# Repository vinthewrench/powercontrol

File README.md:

This repository contains a hardware power controller that enforces safe, predictable power-on and power-off behavior for a Raspberry Pi used in real-world automation systems.

It grew out of the work described in [Raspberry Pi Internet of Things – Part 029](https://www.vinthewrench.com/p/raspberry-pi-internet-of-things-part-029), where the problem wasn’t software, but power: a Pi running irrigation, valves, radios, or sensors cannot simply lose power without consequences. Filesystems corrupt, tasks stop mid-cycle, and batteries get drained dry.

The design documented here takes those ideas further by moving power control out of the Pi and into a small, dedicated controller. The Pi decides when it is safe to shut down; the hardware enforces when power is actually applied or removed. A latching relay does the physical switching, while simple signals coordinate startup, shutdown, and recovery when utility power fails or returns.

The result is a Raspberry Pi that behaves like part of a system, not a hobby board dangling from a power supply.
 
## Repository Layout

```
.
├── Power_Controller_Design_Document_v1.1.md
├── README.md
├── code/
│   └── powercontrol/
│       ├── powercontrol.c
│       ├── makefile
│       └── Doxyfile
└── hw/
    └── powercontrol_2.1/
        ├── powercontrol_2.1.kicad_sch
        ├── powercontrol_2.1.kicad_pcb
        ├── powercontrol_2.1.kicad_pro
        ├── powercontrol_2.1.kicad_prl
        └── build.zip
```

---

## Documentation

### Power_Controller_Design_Document_v1.1.md

This is the **authoritative design specification** for this project.

It defines:
- Hardware intent
- Firmware behavior
- I2C command contract
- Extended readback interface (`0xF0`)
- Design philosophy and explicit non-goals

## Firmware (`code/powercontrol`)

### Overview

The firmware runs on an AVR (ATmega8 / ATmega88 class) and provides:

- Latching relay control (pulse-only, never held)
- Manual wake via INT0
- AC_OK wake via INT1
- Red / Green status LEDs
- I2C slave interface (address `0x08`)
- Watchdog-style host supervision
- Low-power IDLE sleep when inactive

The firmware is **single-loop, flag-driven**, and avoids performing real work in ISRs.

### Files

- `powercontrol.c`  
  Main firmware implementation. This is the source of truth.

- `makefile`  
  Minimal AVR-GCC build file. No build system gymnastics.

- `Doxyfile`  
  Optional Doxygen configuration for generating internal documentation.

### Build

Typical workflow:

```
cd code/powercontrol
make
make flash
```

Target MCU, programmer, and fuses are defined in the makefile and are expected to be adjusted per environment.

## Hardware (`hw/powercontrol_2.1`)

This directory contains the **KiCad revision 2.1** of the Power Controller board.

### Hardware Summary

- +12 V input
- On-board 5 V regulator
- AVR MCU running internal 8 MHz RC oscillator
- ULN2003A relay driver
- Dual-coil latching relay
- Manual wake button
- AC_OK external wake input
- I2C interface with series protection resistors
- Explicit power and ground wiring (no hidden pins)

The MCU remains powered at all times so it can observe wake events even when the downstream system is off.

### Fabrication

`build.zip` contains fabrication outputs (Gerbers, drill files, etc.) suitable for board manufacturing.

## I2C Interface (Summary)

- **Address**: `0x08`
- **Write-only commands** for relay and LED control
- **Extended readback** via command `0xF0`

Example:

```
i2ctransfer -y 1 w1@0x08 0xF0 r4
```

Expected response:

```
0x13 status_byte timer_MSB timer_LSB
```

###  I2C Command Set

| Command | Function |
|-------|----------|
| 0x00 | NO-OP watchdog ping |
| 0x01 | Relay OFF |
| 0x02 | Relay ON |
| 0x03 | Red LED OFF |
| 0x04 | Red LED ON |
| 0x05 | Green LED OFF |
| 0x06 | Green LED ON |
| 0x10 | Set ping timeout (uint16 ms) |

---

## Non-Goals

This project explicitly does **not** attempt to provide:

- RTC or scheduling
- Network connectivity
- Filesystems
- Soft power control
- UPS functionality

Those responsibilities belong on the host system.

## Design Intent (Plain English)

If the host behaves, it stays powered.  
If it locks up, it gets cut off and restarted.  
If a human presses the button, power comes on.  
If AC disappears, the system reacts predictably.

## License

- **Firmware / Software**: MIT License  
- **Hardware designs**: CERN-OHL-P v2 (Permissive Open Hardware Licence)

Copyright © 2026 Vinnie Moscaritolo

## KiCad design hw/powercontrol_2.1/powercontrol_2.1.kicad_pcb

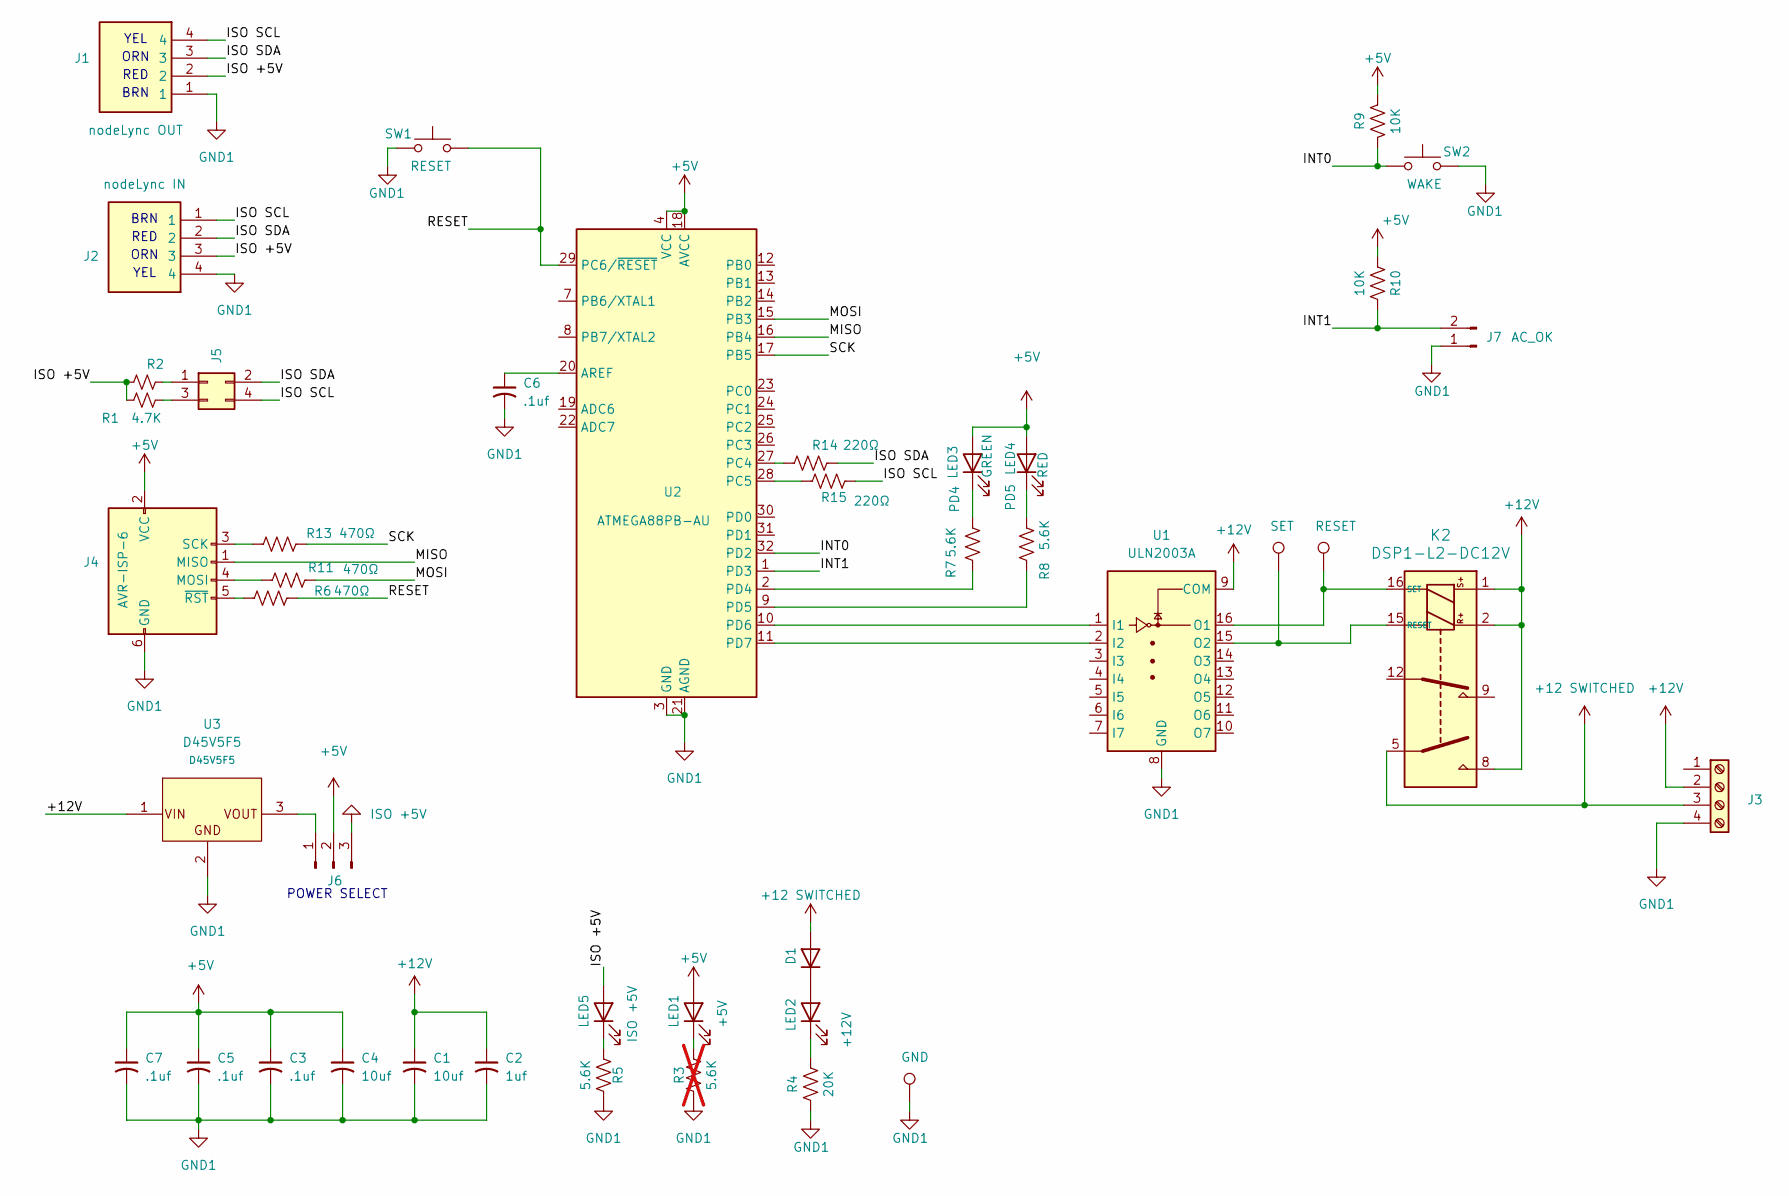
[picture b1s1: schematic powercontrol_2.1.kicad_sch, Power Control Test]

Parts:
C1, C4: 10uf; CP_Radial_D5.0mm_P2.00mm
C2: 1uf; RCER71H104K0DBH03A
C3, C5, C6, C7: .1uf; RCER71H104K0DBH03A
D1: 1N4148WS; D_DO-35_SOD27_P7.62mm_Horizontal
J1, J2: 70551-0003; 705510003; Manufacturer_Part_Number 70551-0003; Mouser Part Number 538-70551-0003
J3: +12; TerminalBlock_Phoenix_MKDS-1,5-4-5.08_1x04_P5.08mm_Horizont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
J4: AVR-ISP-6; PinHeader_2x03_P2.54mm_Vertical
J5: Conn_02x02_Odd_Even; PinHeader_2x02_P2.54mm_Vertical
J6: Conn_01x03_Pin; PinHeader_1x03_P2.54mm_Vertical
J7: Conn_01x02_Pin; PinHeader_1x02_P2.54mm_Vertical
K2: DSP1-L2-DC12V
LED1, LED2, LED3, LED5: 151033GS03000; LED_D3.0mm
LED4: 151033RS03000; LED_D3.0mm
R1, R2: 4.7K; R_Axial_DIN0204_L3.6mm_D1.6mm_P7.62mm_Horizontal
R3: 5.6K; R_Axial_DIN0204_L3.6mm_D1.6mm_P7.62mm_Horizontal; not fitted
R4: 20K; R_Axial_DIN0204_L3.6mm_D1.6mm_P7.62mm_Horizontal
R5, R7, R8: 5.6K; R_Axial_DIN0204_L3.6mm_D1.6mm_P7.62mm_Horizontal
R6, R11, R13: 470Ω; R_Axial_DIN0204_L3.6mm_D1.6mm_P7.62mm_Horizontal
R9, R10: 10K; R_Axial_DIN0204_L3.6mm_D1.6mm_P7.62mm_Horizontal
R14, R15: 220Ω; R_Axial_DIN0204_L3.6mm_D1.6mm_P7.62mm_Horizontal
SW1: RESET; SW_PUSH_6mm
SW2: WAKE; SW_PUSH_6mm
TP1: SET; 5000
TP2: RESET; 5000
TP3: GND; 5000
U1: ULN2003A; DIP-16_W7.62mm
U2: ATMEGA88PB-AU; TQFP-32_7x7mm_P0.8mm
U3: D45V5F5

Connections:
+5V: C3.1, C4.1, C5.1, C7.1, J4.2 (VCC), J6.2, LED1.2 (A), LED3.2 (A), LED4.2 (A), R9.2, R10.2, U2.4 (VCC), U2.6 (VCC), U2.18 (AVCC)
+12 SWITCHED: D1.2 (A), J3.3, K2.5
+12V: C1.1, C2.1, J3.2, K2.1, K2.2, K2.8, U1.9 (COM), U3.1 (VIN)
/INT0: R9.1, SW2.2, U2.32 (PD2)
/INT1: J7.2, R10.1, U2.1 (PD3)
/ISO SCL: J1.4, J2.1, J5.4, R15.1
/ISO SDA: J1.3, J2.2, J5.2, R14.1
/MISO: J4.1 (MISO), U2.16 (PB4)
/MOSI: R11.1, U2.15 (PB3)
/RESET: R6.1, SW1.2, U2.29 (PC6/~RESET)
/SCK: R13.1, U2.17 (PB5)
GND1: C1.2, C2.2, C3.2, C4.2, C5.2, C6.2, C7.2, J1.1, J2.4, J3.4, J4.6 (GND), J7.1, R3.1, R4.2, R5.2, SW1.1, SW2.1, TP3.1, U1.8 (GND), U2.3 (GND), U2.5 (GND), U2.21 (AGND), U3.2 (GND)
ISO +5V: J1.2, J2.3, J6.3, LED5.2 (A), R1.2, R2.2
unnamed: D1.1 (K), LED2.2 (A)
unnamed: J4.4 (MOSI), R11.2
unnamed: J4.3 (SCK), R13.2
unnamed: J4.5 (~RST), R6.2
unnamed: J5.1, R2.1
unnamed: J5.3, R1.1
unnamed: J6.1, U3.3 (VOUT)
unnamed: K2.15 (RESET), TP1.1, U1.15 (O2)
unnamed: K2.16 (SET), TP2.1, U1.16 (O1)
unnamed: LED1.1 (K), R3.2
unnamed: LED2.1 (K), R4.1
unnamed: LED3.1 (K), R7.2
unnamed: LED4.1 (K), R8.2
unnamed: LED5.1 (K), R5.1
unnamed: U1.1 (I1), U2.10 (PD6)
unnamed: U1.2 (I2), U2.11 (PD7)
unnamed: C6.1, U2.20 (AREF)
unnamed: R14.2, U2.27 (PC4)
unnamed: R15.2, U2.28 (PC5)
unnamed: R7.1, U2.2 (PD4)
unnamed: R8.1, U2.9 (PD5)

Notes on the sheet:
ORN
BRN
YEL
RED
POWER SELECT

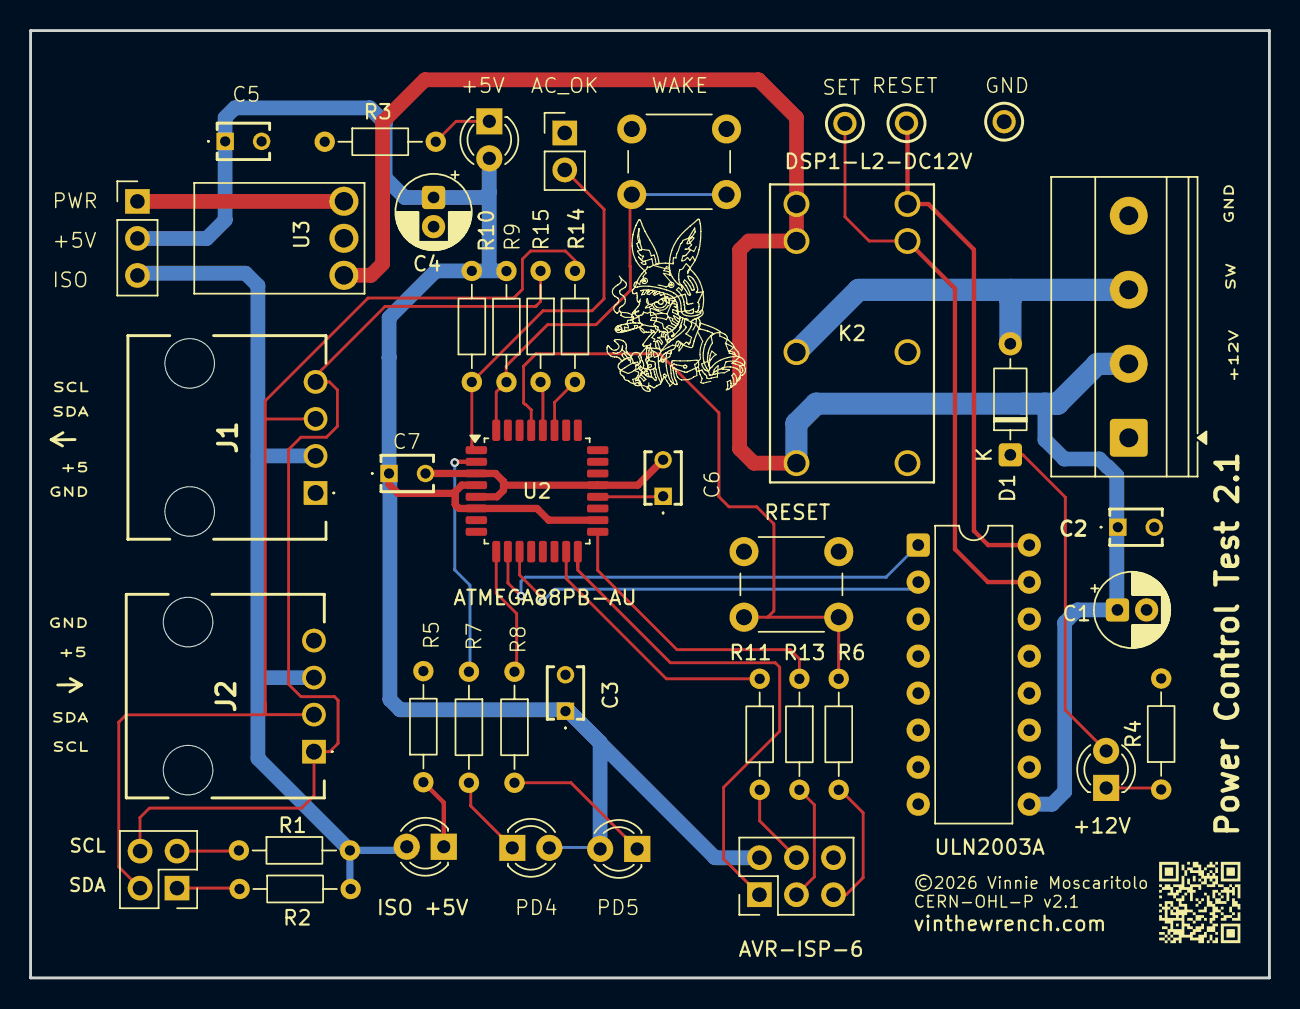
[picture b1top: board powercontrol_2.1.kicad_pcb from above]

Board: 2 copper layers, 85.0 x 65.0 mm, 43 parts (0 on the bottom side), 34 nets.

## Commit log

2026-01-20 initial
2026-01-20 updated read me

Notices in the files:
hw/powercontrol_2.1/powercontrol_2.1.kicad_pcb:
CERN-OHL-P v2.1
